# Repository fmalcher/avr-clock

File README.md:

# Alarm clock with binary output, LCD and DCF77

This project features a working alarm clock with HD44780 compatible display, binary output and DCF77 sync.
It is built using an ATmega16.

Feel free to fork, contribute or ask questions.

## Demonstration

## Issues
* Debouncing does not work correctly
* DCF77 implementation could be much more efficient

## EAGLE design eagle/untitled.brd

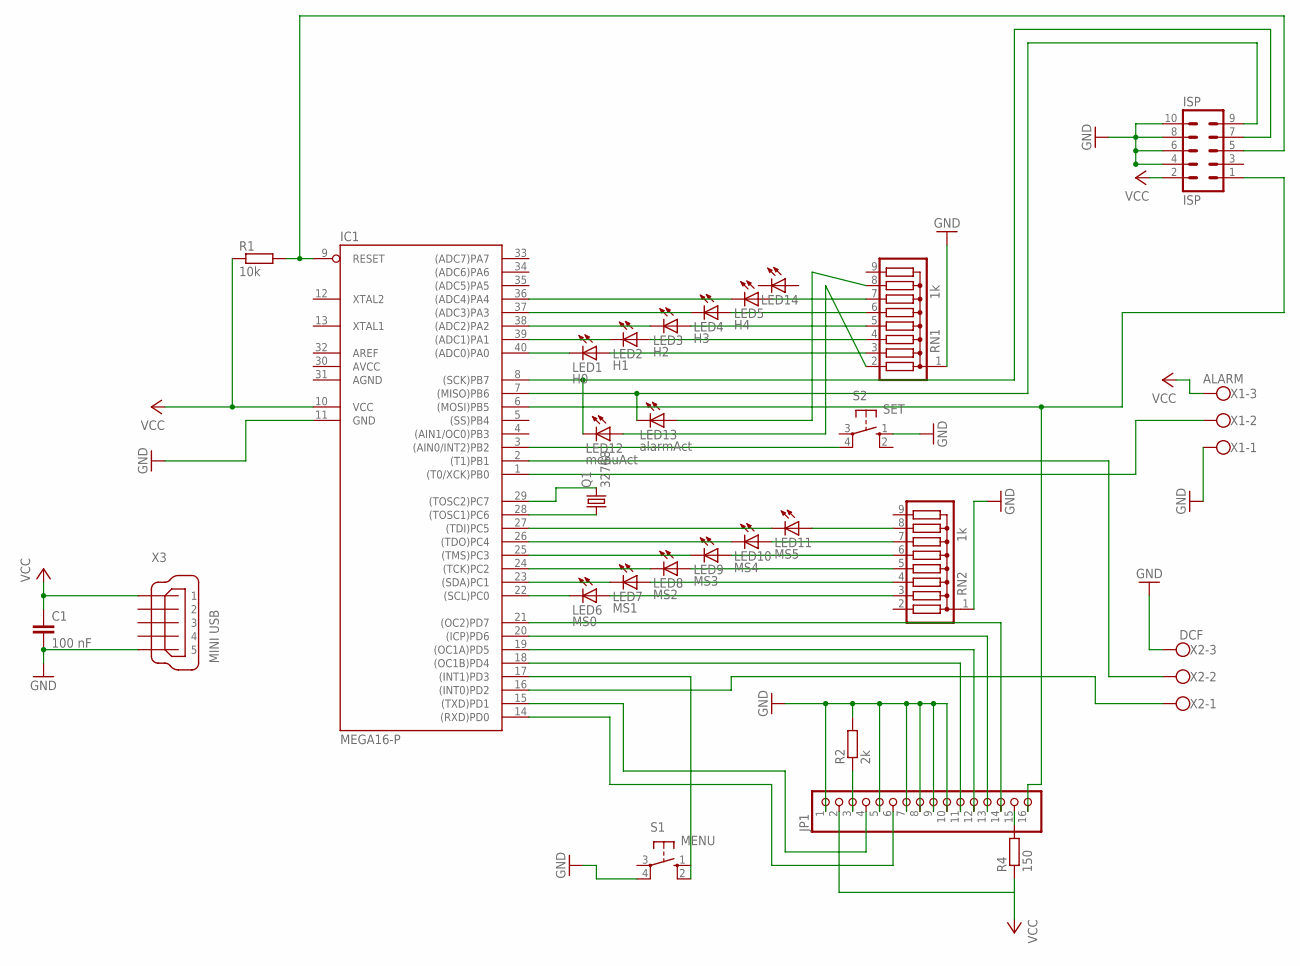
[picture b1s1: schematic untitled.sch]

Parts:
C1: 100 nF; C050-025X075
IC1: MEGA16-P; DIL40
ISP: ISP; ML10
JP1: PINHD-1X16; 1X16
LED1: H0; LED3MM
LED2: H1; LED3MM
LED3: H2; LED3MM
LED4: H3; LED3MM
LED5: H4; LED3MM
LED6: MS0; LED3MM
LED7: MS1; LED3MM
LED8: MS2; LED3MM
LED9: MS3; LED3MM
LED10: MS4; LED3MM
LED11: MS5; LED3MM
LED12: menuAct; LED3MM
LED13: alarmAct; LED3MM
LED14: LED3MM
Q1: 32768; TC26V
R1: 10k; 0207/10
R2: 2k; 0207/10
R4: 150; 0204/7
RN1, RN2: 1k; SIL9
S1: MENU; B3F-10XX
S2: SET; B3F-10XX
X1: ALARM; W237-133
X2: DCF; W237-133
X3: MINI USB; 32005-601

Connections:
AGND: IC1.31 (AGND)
AVCC: IC1.30 (AVCC)
GND: C1.2, IC1.11 (GND), ISP.4, ISP.6, ISP.8, ISP.10, JP1.1, JP1.5, JP1.7, JP1.8, JP1.9, JP1.10, R2.2, RN1.1, RN2.1, S1.4 (P1), S2.1 (S), X1.1, X2.3, X3.5
unnamed: IC1.40 ((ADC0)PA0), LED1.K (C)
unnamed: IC1.39 ((ADC1)PA1), LED2.K (C)
unnamed: IC1.38 ((ADC2)PA2), LED3.K (C)
unnamed: IC1.37 ((ADC3)PA3), LED4.K (C)
unnamed: IC1.36 ((ADC4)PA4), LED5.K (C)
unnamed: IC1.22 ((SCL)PC0), LED6.K (C)
unnamed: IC1.23 ((SDA)PC1), LED7.K (C)
unnamed: IC1.24 ((TCK)PC2), LED8.K (C)
unnamed: IC1.25 ((TMS)PC3), LED9.K (C)
unnamed: IC1.26 ((TDO)PC4), LED10.K (C)
unnamed: IC1.27 ((TDI)PC5), LED11.K (C)
unnamed: IC1.21 ((OC2)PD7), JP1.14
unnamed: LED11.A, RN2.8
unnamed: LED10.A, RN2.7
unnamed: LED9.A, RN2.6
unnamed: LED8.A, RN2.5
unnamed: LED7.A, RN2.4
unnamed: IC1.29 ((TOSC2)PC7), Q1.2
unnamed: IC1.28 ((TOSC1)PC6), Q1.1
unnamed: LED1.A, RN1.3
unnamed: LED2.A, RN1.4
unnamed: LED3.A, RN1.5
unnamed: LED4.A, RN1.6
unnamed: LED5.A, RN1.7
unnamed: IC1.9 (RESET), ISP.5, R1.2
unnamed: IC1.1 ((T0/XCK)PB0), X1.2
unnamed: IC1.6 ((MOSI)PB5), ISP.1, JP1.16
unnamed: IC1.8 ((SCK)PB7), ISP.7, LED12.K (C)
unnamed: LED6.A, RN2.3
unnamed: IC1.20 ((ICP)PD6), JP1.13
unnamed: IC1.19 ((OC1A)PD5), JP1.12
unnamed: IC1.18 ((OC1B)PD4), JP1.11
unnamed: JP1.3, R2.1
unnamed: IC1.15 ((TXD)PD1), JP1.4
unnamed: IC1.17 ((INT1)PD3), S1.2 (S1)
unnamed: IC1.14 ((RXD)PD0), JP1.6
unnamed: IC1.7 ((MISO)PB6), ISP.9, LED13.K (C)
unnamed: IC1.16 ((INT0)PD2), X2.1
unnamed: IC1.2 ((T1)PB1), X2.2
unnamed: LED12.A, RN1.2
unnamed: LED13.A, RN1.8
unnamed: IC1.3 ((AIN0/INT2)PB2), S2.4 (P1)
unnamed: JP1.15, R4.2
VCC: C1.1, IC1.10 (VCC), ISP.2, JP1.2, R1.1, R4.1, X1.3, X3.1

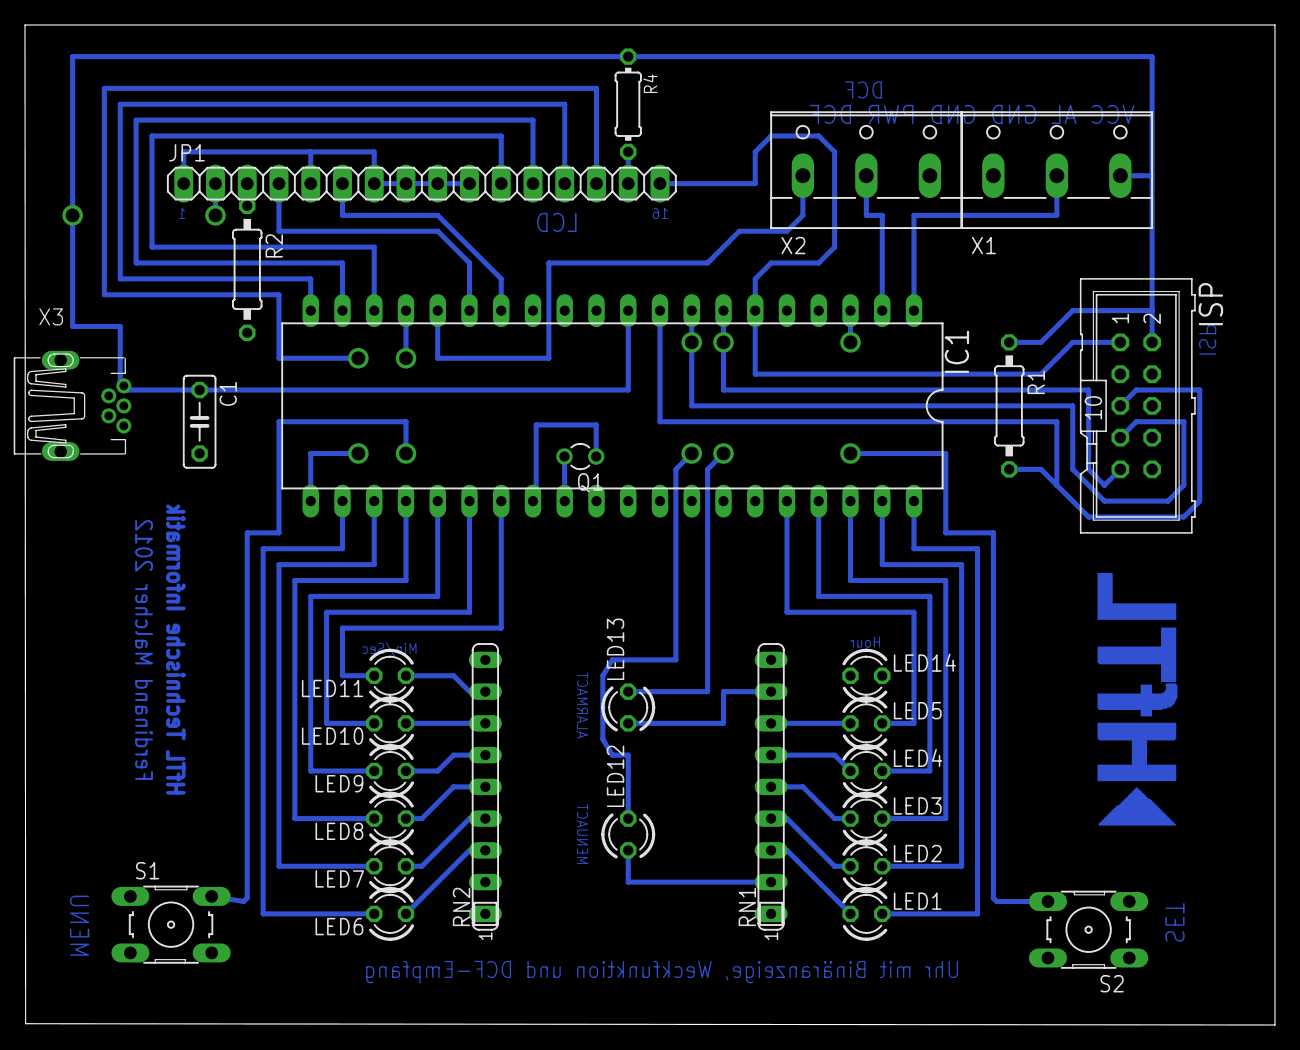
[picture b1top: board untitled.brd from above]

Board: 2 copper layers, 100.0 x 80.0 mm, 29 parts (0 on the bottom side), 45 nets.

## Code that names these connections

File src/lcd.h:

// Ansteuerung eines HD44780 kompatiblen LCD im 4-Bit-Interfacemodus
// http://www.mikrocontroller.net/articles/AVR-GCC-Tutorial/LCD-Ansteuerung
//
 
#ifndef LCD_ROUTINES_H
#define LCD_ROUTINES_H

#include <avr/pgmspace.h>
////////////////////////////////////////////////////////////////////////////////
// Pinbelegung für das LCD, an verwendete Pins anpassen
// alle Pins müssen in einem Port liegen
// die 4 Bit für die Daten müssen zusammenliegen, können aber an einer
// beliebigen Postion anfangen  
 
//  LCD DB4-DB7 <-->  PORTD Bit PD4-PD7
#define LCD_PORT      PORTD
#define LCD_DDR       DDRD

// LCD Datenbus, Bitnummer des untersten Bits D4, kann auf den
// Portbits 0..4 liegen

#define LCD_DB        PD4
 
//  LCD RS      <-->  PORTD Bit PD2     (RS: 0=Data, 1=Command)
#define LCD_RS        PD1
 
//  LCD EN      <-->  PORTD Bit PD3     (EN: 1-Impuls für Daten)
#define LCD_EN        PD0
 
////////////////////////////////////////////////////////////////////////////////
// LCD Ausführungszeiten (MS=Millisekunden, US=Mikrosekunden)
 
#define LCD_BOOTUP_MS           15
#define LCD_ENABLE_US           1
#define LCD_WRITEDATA_US        46
#define LCD_COMMAND_US          42
 
#define LCD_SOFT_RESET_MS1      5
#define LCD_SOFT_RESET_MS2      1
#define LCD_SOFT_RESET_MS3      1
#define LCD_SET_4BITMODE_MS     5
 
#define LCD_CLEAR_DISPLAY_MS    2
#define LCD_CURSOR_HOME_MS      2
 
////////////////////////////////////////////////////////////////////////////////
// Zeilendefinitionen des verwendeten LCD
// Die Einträge hier sollten für ein LCD mit einer Zeilenlänge von 16 Zeichen passen
// Bei anderen Zeilenlängen müssen diese Einträge angepasst werden
 
#define LCD_DDADR_LINE1         0x00
#define LCD_DDADR_LINE2         0x40
#define LCD_DDADR_LINE3         0x10
#define LCD_DDADR_LINE4         0x50
 
////////////////////////////////////////////////////////////////////////////////
// Initialisierung: muss ganz am Anfang des Programms aufgerufen werden.
void lcd_init( void );
 
////////////////////////////////////////////////////////////////////////////////
// LCD löschen
void lcd_clear( void );
 
////////////////////////////////////////////////////////////////////////////////
// Cursor in die 1. Zeile, 0-te Spalte
void lcd_home( void );
 
////////////////////////////////////////////////////////////////////////////////
// Cursor an eine beliebige Position 
void lcd_setcursor( uint8_t spalte, uint8_t zeile );
 
////////////////////////////////////////////////////////////////////////////////
// Ausgabe eines einzelnen Zeichens an der aktuellen Cursorposition 
void lcd_data( uint8_t data );
 
////////////////////////////////////////////////////////////////////////////////
// Ausgabe eines Strings an der aktuellen Cursorposition 
// String liegt im RAM
void lcd_string( const char *data );

////////////////////////////////////////////////////////////////////////////////
// Ausgabe eines Strings an der aktuellen Cursorposition
// String liegt im Flash 
void lcd_string_P( PGM_P data );
 
////////////////////////////////////////////////////////////////////////////////
// Definition eines benutzerdefinierten Sonderzeichens.
// data muss auf ein Array[8] mit den Zeilencodes des zu definierenden Zeichens
// zeigen, Daten liegen im RAM
void lcd_generatechar( uint8_t code, const uint8_t *data );
 
////////////////////////////////////////////////////////////////////////////////
// Definition eines benutzerdefinierten Sonderzeichens.
// data muss auf ein Array[8] mit den Zeilencodes des zu definierenden Zeichens
// zeigen, Daten liegen im FLASH
void lcd_generatechar_P( uint8_t code, PGM_P data );
 
////////////////////////////////////////////////////////////////////////////////
// Ausgabe eines Kommandos an das LCD.
void lcd_command( uint8_t data );

////////////////////////////////////////////////////////////////////////////////
// LCD Befehle und Argumente.
// Zur Verwendung in lcd_command
 
// Clear Display -------------- 0b00000001
#define LCD_CLEAR_DISPLAY       0x01
 
// Cursor Home ---------------- 0b0000001x
#define LCD_CURSOR_HOME         0x02
 
// Set Entry Mode ------------- 0b000001xx
#define LCD_SET_ENTRY           0x04
 
#define LCD_ENTRY_DECREASE      0x00
#define LCD_ENTRY_INCREASE      0x02
#define LCD_ENTRY_NOSHIFT       0x00
#define LCD_ENTRY_SHIFT         0x01
 
// Set Display ---------------- 0b00001xxx
#define LCD_SET_DISPLAY         0x08
 
#define LCD_DISPLAY_OFF         0x00
#define LCD_DISPLAY_ON          0x04
#define LCD_CURSOR_OFF          0x00
#define LCD_CURSOR_ON           0x02
#define LCD_BLINKING_OFF        0x00
#define LCD_BLINKING_ON         0x01
 
// Set Shift ------------------ 0b0001xxxx
#define LCD_SET_SHIFT           0x10
 
#define LCD_CURSOR_MOVE         0x00
#define LCD_DISPLAY_SHIFT       0x08
#define LCD_SHIFT_LEFT          0x00
#define LCD_SHIFT_RIGHT         0x01
 
// Set Function --------------- 0b001xxxxx
#define LCD_SET_FUNCTION        0x20
 
#define LCD_FUNCTION_4BIT       0x00
#define LCD_FUNCTION_8BIT       0x10
#define LCD_FUNCTION_1LINE      0x00
#define LCD_FUNCTION_2LINE      0x08
#define LCD_FUNCTION_5X7        0x00
#define LCD_FUNCTION_5X10       0x04
 
#define LCD_SOFT_RESET          0x30
 
// Set CG RAM Address --------- 0b01xxxxxx  (Character Generator RAM)
#define LCD_SET_CGADR           0x40
 
#define LCD_GC_CHAR0            0
#define LCD_GC_CHAR1            1
#define LCD_GC_CHAR2            2
#define LCD_GC_CHAR3            3
#define LCD_GC_CHAR4            4
#define LCD_GC_CHAR5            5
#define LCD_GC_CHAR6            6
#define LCD_GC_CHAR7            7
 
// Set DD RAM Address --------- 0b1xxxxxxx  (Display Data RAM)
#define LCD_SET_DDADR           0x80
 
#endif 
